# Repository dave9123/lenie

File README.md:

# Lenie
A smart alarm clock that helps you reduce distractions and reminds you about upcoming tasks.

## Origin
_Lenie means “of Magdala”_ (from Magdalena) and “torch”, “beautiful”, “light”, “bright” and “shining” (from Helene).

## Goals
- Support music playback
- Support alarms
- Support reminders
- Integrate with my [ReminderAPI](https://reminderapi.dave9123.me/)
- Be able to import events from calendars and to do
	- [Google Calendar](https://calendar.google.com/)
		- https://developers.google.com/workspace/calendar/api/guides/overview
	- [Google Tasks](https://tasks.google.com)
		- https://developers.google.com/workspace/tasks/reference/rest
	- [Microsoft To Do](https://to-do.live.com/tasks/)
		- https://learn.microsoft.com/en-us/graph/api/resources/todo-overview?view=graph-rest-1.0
	- [Outlook Calendar](https://outlook.live.com/calendar/)
		- https://learn.microsoft.com/en-us/graph/api/resources/calendar-overview?view=graph-rest-1.0
	- [Todoist](https://app.todoist.com/app)
		- https://developer.todoist.com/api/v1/

## Attributions
- <a href="https://www.flaticon.com/free-icons/weather" title="weather icons">Weather icons created by iconixar - Flaticon</a>
- <a href="https://www.flaticon.com/free-icons/sunny" title="sunny icons">Sunny icons created by Freepik - Flaticon</a>
- <a href="https://www.flaticon.com/free-icons/rain" title="rain icons">Rain icons created by apien - Flaticon</a>
- <a href="https://www.flaticon.com/free-icons/list" title="list icons">List icons created by Freepik - Flaticon</a>
- https://www.reddit.com/r/NoStupidQuestions/comments/1h9wh2m/is_it_bad_to_sleep_with_red_leds/

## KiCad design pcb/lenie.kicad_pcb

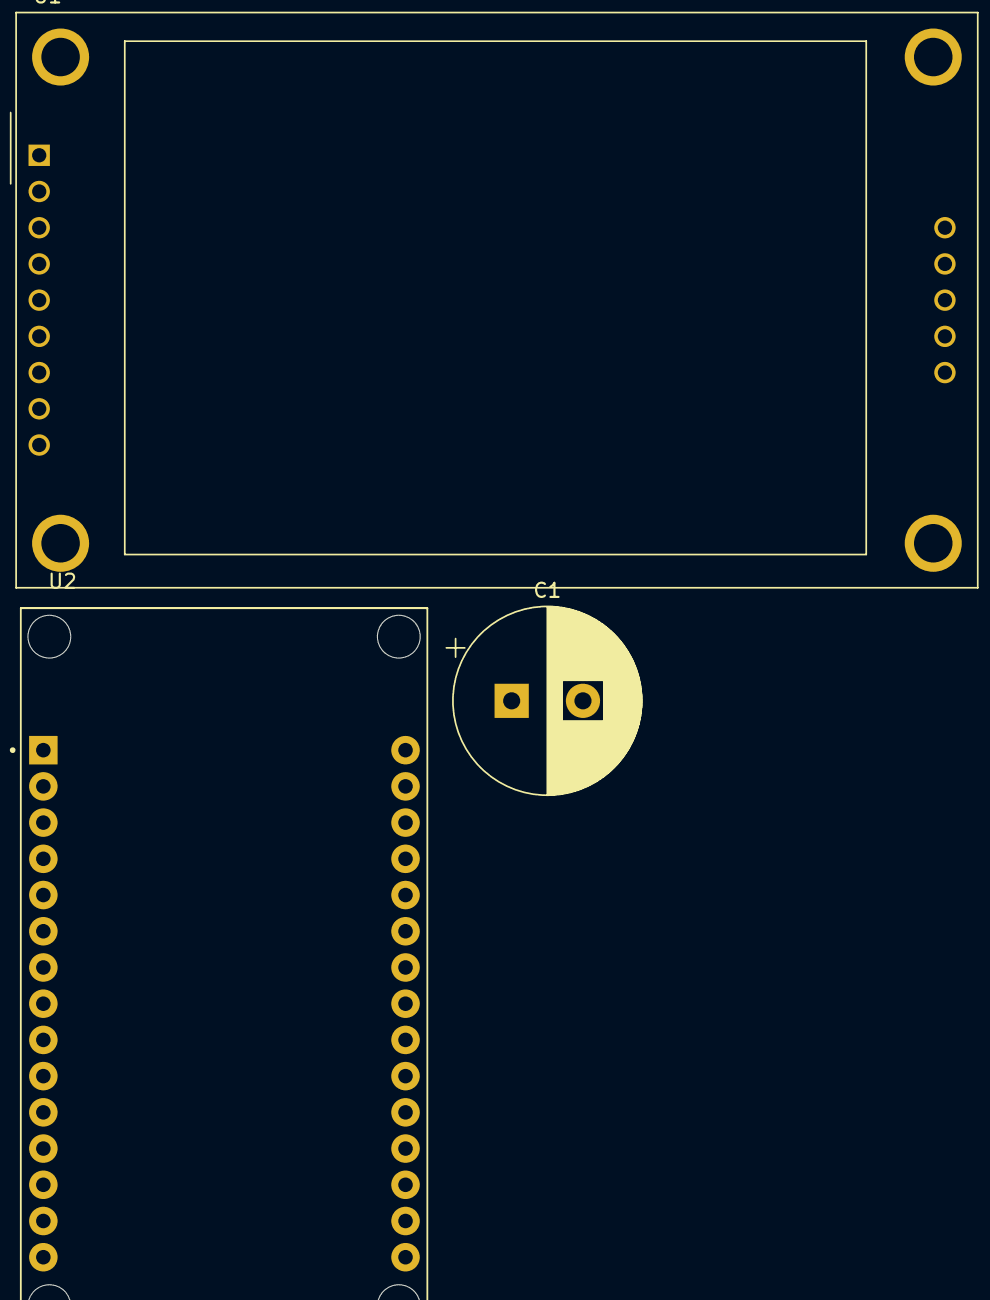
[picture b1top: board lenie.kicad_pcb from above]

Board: 2 copper layers, 3 parts (0 on the bottom side), 12 nets, no tracks yet.

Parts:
C1: 2200uF 25V; CP_Radial_D13.0mm_P5.00mm
U1: CR2013-MI2120
U2: ESP32-DEVKIT-V1; MODULE_ESP32_DEVKIT_V1

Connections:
+3V3: U1.1 (VCC), U2.1 (3V3)
-BATT: C1.2, U1.2 (GND), U2.2 (GND), U2.29 (GND)
MISO: U1.9 (MISO), U1.12 (SD_MISO), U2.27 (D12)
MOSI: U1.6 (MOSI), U1.11 (SD_MOSI), U2.28 (D13)
SCK: U1.7 (SCK), U1.13 (SD_SCK), U2.26 (D14)
SD_CS: U1.10 (SD_CS), U2.8 (D5)
SD_DETECT: U1.14 (FLASH_CD), U2.19 (D34)
TFT_CS: U1.3 (~CS), U2.3 (D15)
TFT_DC: U1.5 (D/~C), U2.4 (D2)
TFT_LED: U1.8 (LED), U2.10 (D19)
TFT_RST: U1.4 (RESET), U2.5 (D4)
VCC: C1.1, U2.30 (VIN)

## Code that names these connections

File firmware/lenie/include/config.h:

#ifndef LENIE_CONFIG_H
#define LENIE_CONFIG_H

#define WIFI_SETUP_SSID "Lenie" // Runs as AP for onboarding, 32 characters max
// #define WIFI_PASSWORD_OVERRIDE "" // Uncomment this to override automatic password generation
#define WIFI_HOSTNAME "lenie" // 253 ASCII characters max, may contain only the ASCII letters a-z (in a case-insensitive manner), the digits 0-9, and the hyphen-minus character ('-')

#define TIMEZONE_OVERRIDE "Asia/Jakarta"

#define BATTERY_MAX_VOLTAGE 4.2
#define BATTERY_MIN_VOLTAGE 3.0
#define BATTERY_DIVIDER_RATIO (470/1470)

#define BUTTON_1 23
#define BUTTON_2 27
#define BUTTON_3 32
#define BUTTON_4 33
#define BUTTON_5 35

#define TFT_DC 2
#define TFT_CS 15
#define TFT_SCLK 14
#define TFT_MOSI 13
#define TFT_MISO 12
#define TFT_RST 4
#define TFT_BL 18

#define SD_CS 5
#define SD_MOSI 13
#define SD_MISO 12
#define SD_SCK 14
#define SD_DETECT 34

#define LED_DIN 12
#define LED_CS 19
#define LED_SCK 14

#define PAM8403_L 25
#define PAM8403_R 26

#define DS3231_SCL 22
#define DS3231_SDA 21

#define BATTERY_LEVEL 36

#endif

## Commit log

2025-05-24 vault backup: 2025-05-24 19:55:00
2025-05-26 vault backup: 2025-05-26 20:39:21
2025-05-26 vault backup: 2025-05-26 20:45:42
2025-05-28 vault backup: 2025-05-28 22:00:58
2025-06-01 vault backup: 2025-06-01 16:34:12
2025-06-07 some code
